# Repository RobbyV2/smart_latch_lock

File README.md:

# Folding-Arc Bike Lock

A self-closing bike lock built as a clamshell ring. A fixed arc bolts to the housing, a hinged arc swings 180 degrees to meet it, and a worm gearmotor closes the loop around the frame and rim on a button press or a BLE command. A spring latch pin seats with power off, a keyed cam lock covers a dead battery, and an ESP32-C3 on a 4-layer PCB runs the state machine.

<table>
<tr>
<td></td>
<td></td>
</tr>
</table>

The animation shows one closing cycle: the swing arc starts folded open and sweeps around until it seats in the receiver at the fixed arc tip.

<table>
<tr>
<td></td>
<td></td>
<td></td>
</tr>
</table>

Read `docs/design.md` for the mechanism, the torque analysis, and the electronics.

## Repository layout

- `hw/` holds the KiCad schematic, the board, the design rules, and the stack manifest.
- `lib/` holds the symbols, the footprints, and the 3D models.
- `firmware/` holds the PlatformIO project for the ESP32-C3.
- `3d/` holds the OpenSCAD housing, the board render script, and the renders.
- `scripts/` holds the release script and the validation scripts.
- `fab/` holds the fabrication data, written by `scripts/release.sh`.

## Build

```
pio run -d firmware
openscad -o temp/arc_swing.stl -D 'part="arc_swing"' 3d/housing.scad
python3 3d/build.py
scripts/release.sh hw/triangle_flywheel_balancer.kicad_pcb
```

The first command builds the firmware, the second renders one housing part (`housing_inner`, `housing_lid`, `arc_fixed`, `arc_swing`, `latch_pin`, `assembly`), the third writes the board renders and the viewer page, and the fourth writes the fabrication tree.

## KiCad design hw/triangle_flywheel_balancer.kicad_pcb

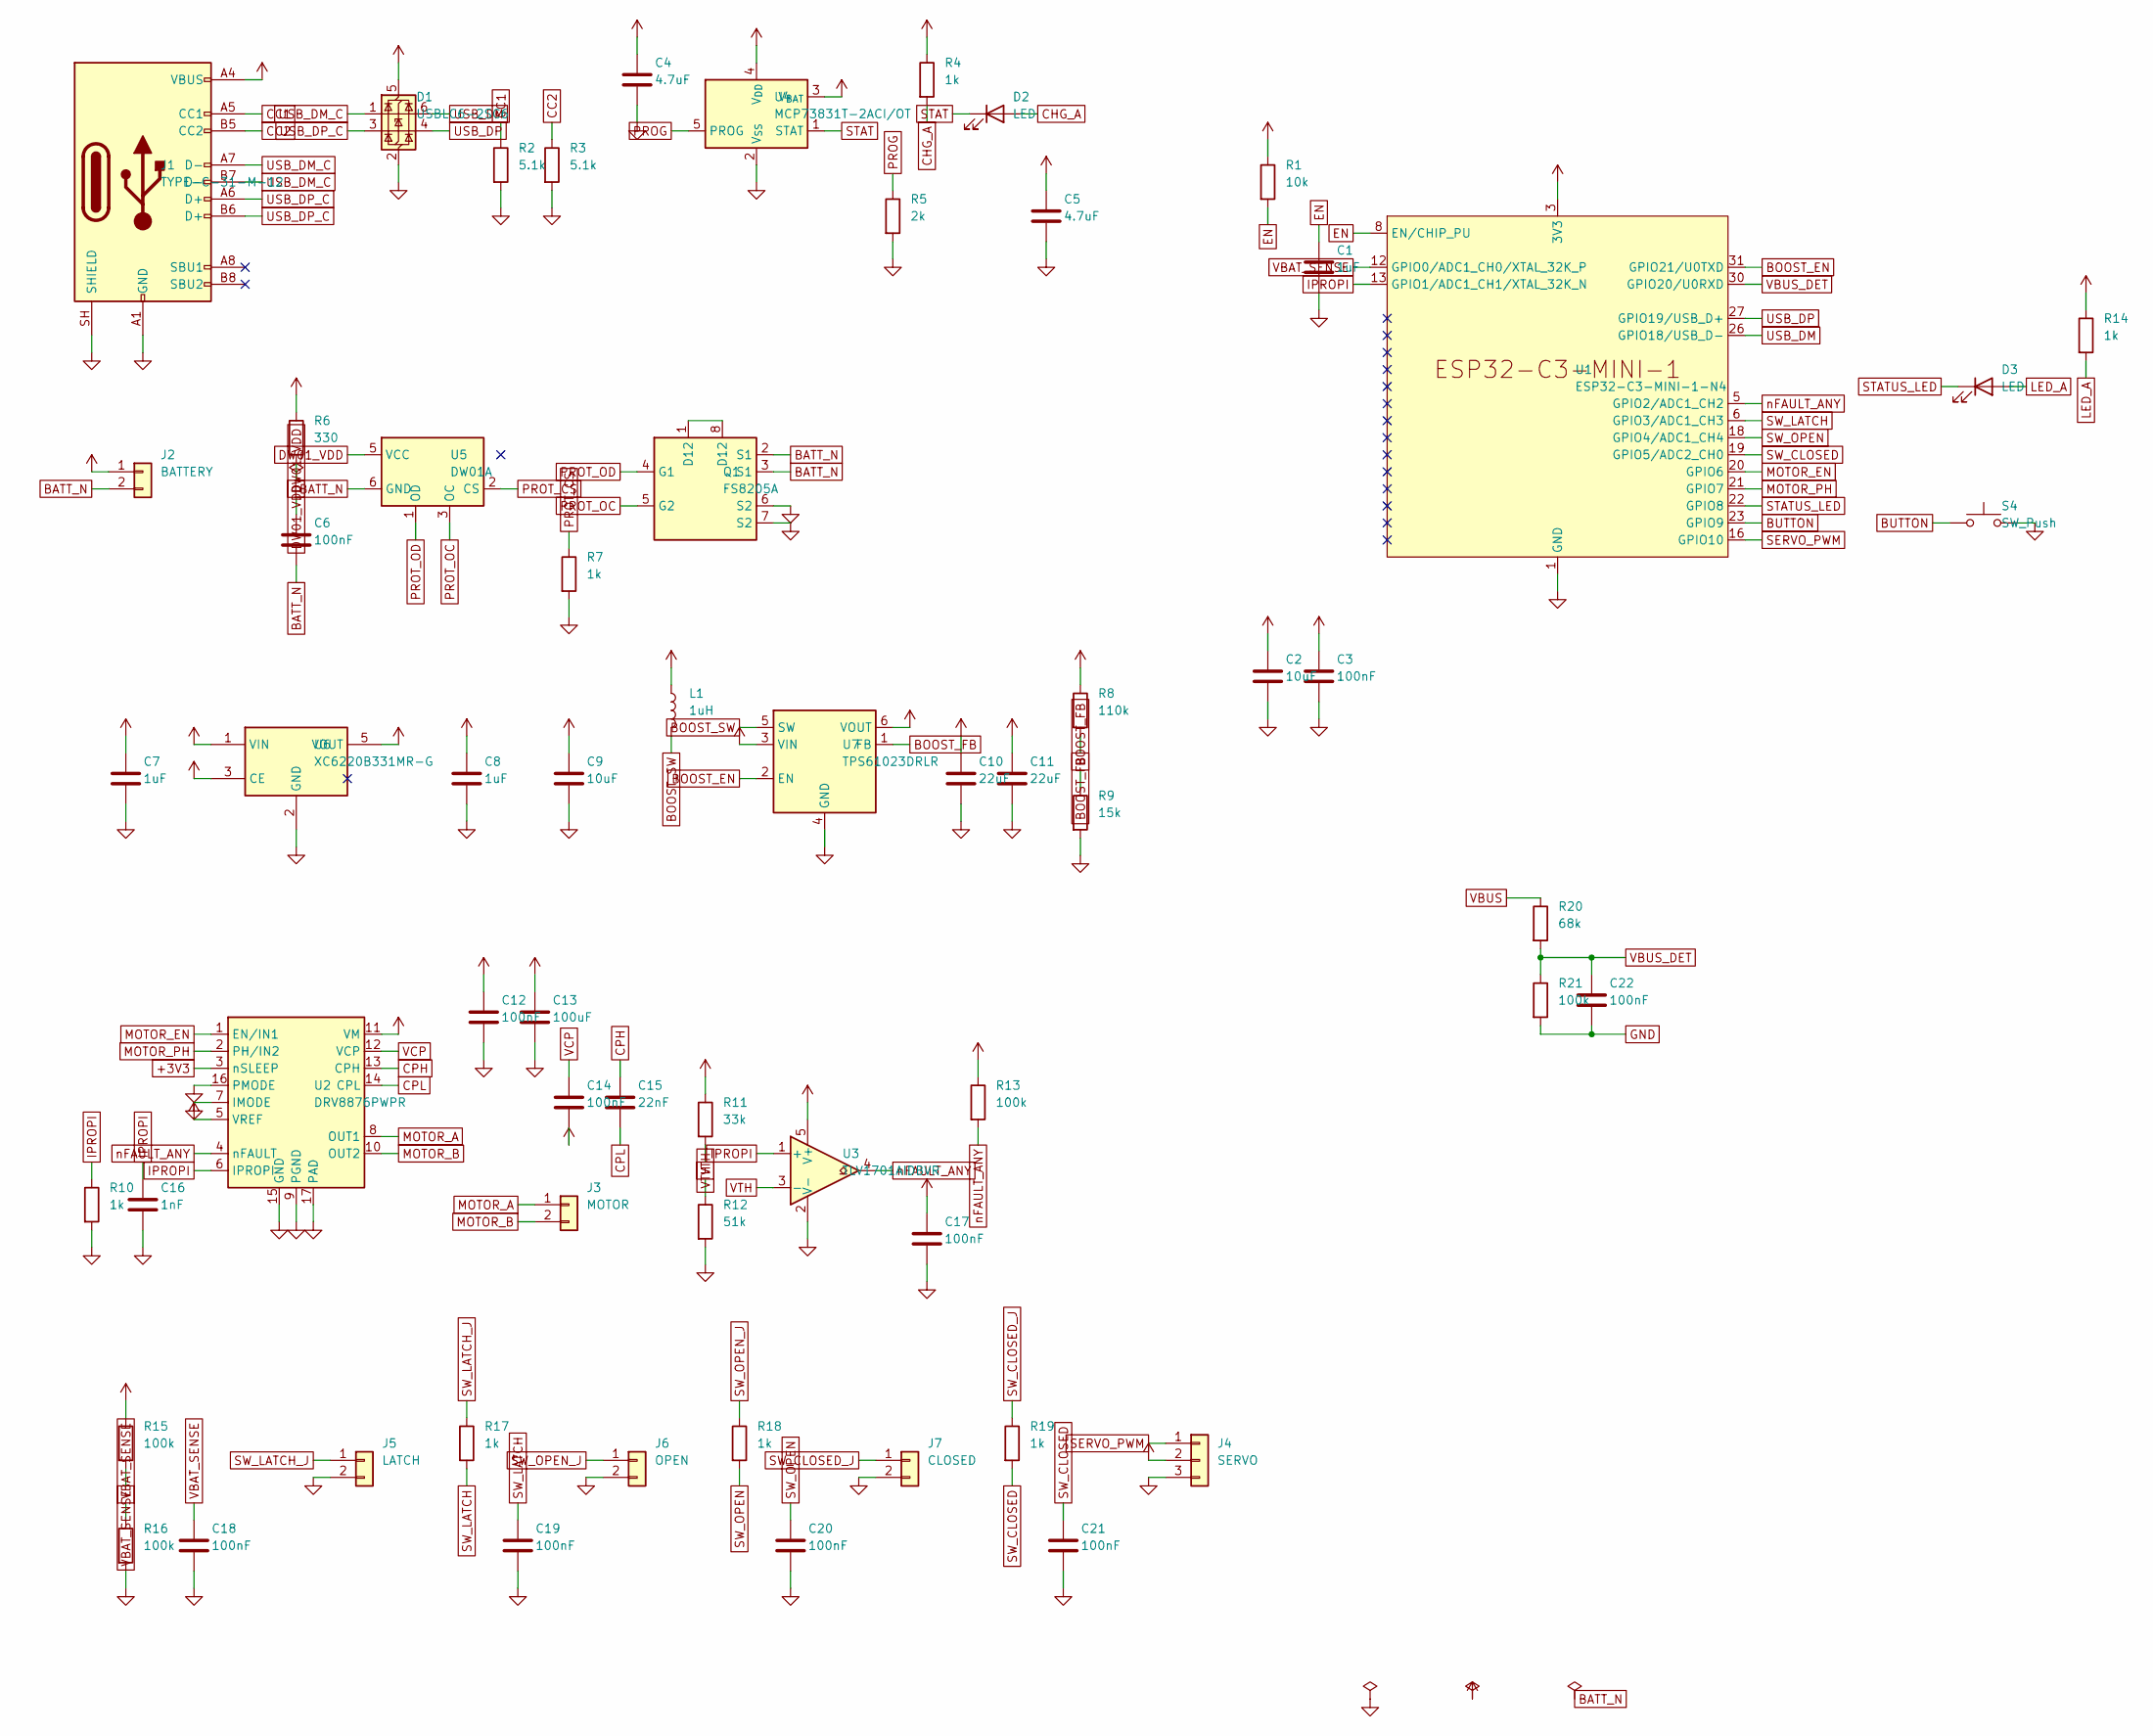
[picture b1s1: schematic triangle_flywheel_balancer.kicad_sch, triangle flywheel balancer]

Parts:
C1, C7, C8: 1uF; C_0603_1608Metric; MPN CL10A105KB8NNNC; LCSC Part C15849
C2, C9: 10uF; C_0805_2012Metric; MPN CL21A106KAYNNNE; LCSC Part C15850
C3, C6, C12, C14, C17, C18, C19, C20, C21, C22: 100nF; C_0402_1005Metric; MPN CL05B104KO5NNNC; LCSC Part C1525
C4, C5: 4.7uF; C_0603_1608Metric; MPN CL10A475KO8NNNC; LCSC Part C19666
C10, C11: 22uF; C_0805_2012Metric; MPN CL21A226MAQNNNE; LCSC Part C45783
C13: 100uF; C_1210_3225Metric; MPN CL32A107MPVNNNE; LCSC Part C23742
C15: 22nF; C_0402_1005Metric; MPN CL05B223KB5NNNC; LCSC Part C337699
C16: 1nF; C_0402_1005Metric; MPN 0402B102K500NT; LCSC Part C1523
D1: USBLC6-2SC6; SOT-23-6; MPN USBLC6-2SC6; LCSC Part C7519
D2, D3: LED; LED_0603_1608Metric; MPN KT-0603R; LCSC Part C2286
J1: TYPE-C-31-M-12; USB_C_Receptacle_HRO_TYPE-C-31-M-12; MPN TYPE-C-31-M-12; LCSC Part C165948
J2: BATTERY; JST_PH_B2B-PH-K_1x02_P2.00mm_Vertical; MPN B2B-PH-K-S(LF)(SN); LCSC Part C131337
J3: MOTOR; JST_PH_B2B-PH-K_1x02_P2.00mm_Vertical; MPN B2B-PH-K-S(LF)(SN); LCSC Part C131337
J4: SERVO; PinHeader_1x03_P2.54mm_Vertical; MPN 2.54-1*3P; LCSC Part C49257
J5: LATCH; PinHeader_1x02_P2.54mm_Vertical; MPN B-2100S02P-A110; LCSC Part C124375
J6: OPEN; PinHeader_1x02_P2.54mm_Vertical; MPN B-2100S02P-A110; LCSC Part C124375
J7: CLOSED; PinHeader_1x02_P2.54mm_Vertical; MPN B-2100S02P-A110; LCSC Part C124375
L1: 1uH; L_Murata_DFE201610P; MPN DFE201610E-1R0M=P2; LCSC Part C161082
Q1: FS8205A; TSSOP-8_4.4x3mm_P0.65mm; MPN 8205A; LCSC Part C5148694
R1: 10k; R_0402_1005Metric; MPN RC0402FR-0710KL; LCSC Part C60490
R2, R3: 5.1k; R_0402_1005Metric; MPN 0402WGF5101TCE; LCSC Part C25905
R4, R7, R10, R14, R17, R18, R19: 1k; R_0402_1005Metric; MPN 0402WGF1001TCE; LCSC Part C11702
R5: 2k; R_0402_1005Metric; MPN RC0402FR-072KL; LCSC Part C60488
R6: 330; R_0402_1005Metric; MPN 0402WGF3300TCE; LCSC Part C25104
R8: 110k; R_0402_1005Metric; MPN 0402WGF1103TCE; LCSC Part C25745
R9: 15k; R_0402_1005Metric; MPN 0402WGF1502TCE; LCSC Part C25756
R11: 33k; R_0402_1005Metric; MPN 0402WGF3302TCE; LCSC Part C25779
R12: 51k; R_0402_1005Metric; MPN 0402WGF5102TCE; LCSC Part C25794
R13, R15, R16, R21: 100k; R_0402_1005Metric; MPN 0402WGF1003TCE; LCSC Part C25741
R20: 68k; R_0402_1005Metric; MPN ERJ2RKF6802X; LCSC Part C77607
S4: SW_Push; SW_Push_1TS009xxxx-xxxx-xxxx_6x6x5mm; MPN TS-1187A-B-A-B; LCSC Part C318884
U1: ESP32-C3-MINI-1-N4; ESP32-C3-MINI-1; MPN ESP32-C3-MINI-1-N4; LCSC Part C2838502
U2: DRV8876PWPR; HTSSOP-16-1EP_4.4x5mm_P0.65mm_EP3.4x5mm_Mask3x3mm_ThermalVi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; MPN DRV8876PWPR; LCSC Part C575551
U3: TLV1701AIDBVR; SOT-23-5; MPN TLV1701AIDBVR; LCSC Part C130035
U4: MCP73831T-2ACI/OT; SOT-23-5; MPN MCP73831T-2ACI/OT; LCSC Part C424093
U5: DW01A; SOT-23-6; MPN DW01A; LCSC Part C351410
U6: XC6220B331MR-G; SOT-23-5; MPN XC6220B331MR-G; LCSC Part C86534
U7: TPS61023DRLR; SOT-563; MPN TPS61023DRLR; LCSC Part C919459

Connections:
+3V3: C2.1, C3.1, C8.1, C17.1, R1.1, R11.1, R13.1, R14.1, U1.3 (3V3), U2.3 (nSLEEP), U2.5 (VREF), U3.5 (V+), U6.5 (VOUT)
+5V: C10.1, C11.1, C12.1, C13.1, C14.2, J4.2, R8.1, U2.11 (VM), U7.6 (VOUT)
BATT_N: C6.2, J2.2, Q1.2 (S1), Q1.3 (S1), U5.6 (GND)
BOOST_EN: U1.31 (GPIO21/U0TXD), U7.2 (EN)
BOOST_FB: R8.2, R9.1, U7.1 (FB)
BOOST_SW: L1.2, U7.5 (SW)
BUTTON: S4.1, U1.23 (GPIO9)
CC1: J1.A5 (CC1), R2.1
CC2: J1.B5 (CC2), R3.1
CHG_A: D2.2 (A), R4.2
CPH: C15.1, U2.13 (CPH)
CPL: C15.2, U2.14 (CPL)
DW01_VDD: C6.1, R6.2, U5.5 (VCC)
EN: C1.1, R1.2, U1.8 (EN/CHIP_PU)
GND: C1.2, C2.2, C3.2, C4.2, C5.2, C7.2, C8.2, C9.2, C10.2, C11.2, C12.2, C13.2, C16.2, C17.2, C18.2, C19.2, C20.2, C21.2, C22.2, D1.2 (GND), J1.A1 (GND), J1.A12 (GND), J1.B1 (GND), J1.B12 (GND), J1.SH (SHIELD), J4.3, J5.2, J6.2, J7.2, Q1.6 (S2), Q1.7 (S2), R2.2, R3.2, R5.2, R7.2, R9.2, R10.2, R12.2, R16.2, R21.2, S4.2, U1.1 (GND), U1.2 (GND), U1.11 (GND), U1.14 (GND), U1.36 (GND), U1.37 (GND), U1.38 (GND), U1.39 (GND), U1.40 (GND), U1.41 (GND), U1.42 (GND), U1.43 (GND), U1.44 (GND), U1.45 (GND), U1.46 (GND), U1.47 (GND), U1.48 (GND), U1.49 (GND), U1.50 (GND), U1.51 (GND), U1.52 (GND), U1.53 (GND), U2.7 (IMODE), U2.9 (PGND), U2.15 (GND), U2.16 (PMODE), U2.17 (PAD), U3.2 (V-), U4.2 (V_{SS}), U6.2 (GND), U7.4 (GND)
IPROPI: C16.1, R10.1, U1.13 (GPIO1/ADC1_CH1/XTAL_32K_N), U2.6 (IPROPI), U3.1 (+)
LED_A: D3.2 (A), R14.2
MOTOR_A: J3.1, U2.8 (OUT1)
MOTOR_B: J3.2, U2.10 (OUT2)
MOTOR_EN: U1.20 (GPIO6), U2.1 (EN/IN1)
MOTOR_PH: U1.21 (GPIO7), U2.2 (PH/IN2)
unnamed: Q1.1 (D12), Q1.8 (D12)
PROG: R5.1, U4.5 (PROG)
PROT_CS: R7.1, U5.2 (CS)
PROT_OC: Q1.5 (G2), U5.3 (OC)
PROT_OD: Q1.4 (G1), U5.1 (OD)
SERVO_PWM: J4.1, U1.16 (GPIO10)
STAT: D2.1 (K), U4.1 (STAT)
STATUS_LED: D3.1 (K), U1.22 (GPIO8)
SW_CLOSED: C21.1, R19.2, U1.19 (GPIO5/ADC2_CH0)
SW_CLOSED_J: J7.1, R19.1
SW_LATCH: C19.1, R17.2, U1.6 (GPIO3/ADC1_CH3)
SW_LATCH_J: J5.1, R17.1
SW_OPEN: C20.1, R18.2, U1.18 (GPIO4/ADC1_CH4)
SW_OPEN_J: J6.1, R18.1
USB_DM: D1.6 (I/O1), U1.26 (GPIO18/USB_D-)
USB_DM_C: D1.1 (I/O1), J1.A7 (D-), J1.B7 (D-)
USB_DP: D1.4 (I/O2), U1.27 (GPIO19/USB_D+)
USB_DP_C: D1.3 (I/O2), J1.A6 (D+), J1.B6 (D+)
VBAT: C5.1, C7.1, C9.1, J2.1, L1.1, R6.1, R15.1, U4.3 (V_{BAT}), U6.1 (VIN), U6.3 (CE), U7.3 (VIN)
VBAT_SENSE: C18.1, R15.2, R16.1, U1.12 (GPIO0/ADC1_CH0/XTAL_32K_P)
VBUS: C4.1, D1.5 (VBUS), J1.A4 (VBUS), J1.A9 (VBUS), J1.B4 (VBUS), J1.B9 (VBUS), R4.1, R20.1, U4.4 (V_{DD})
VBUS_DET: C22.1, R20.2, R21.1, U1.30 (GPIO20/U0RXD)
VCP: C14.1, U2.12 (VCP)
VTH: R11.2, R12.1, U3.3 (-)
nFAULT_ANY: R13.2, U1.5 (GPIO2/ADC1_CH2), U2.4 (nFAULT), U3.4

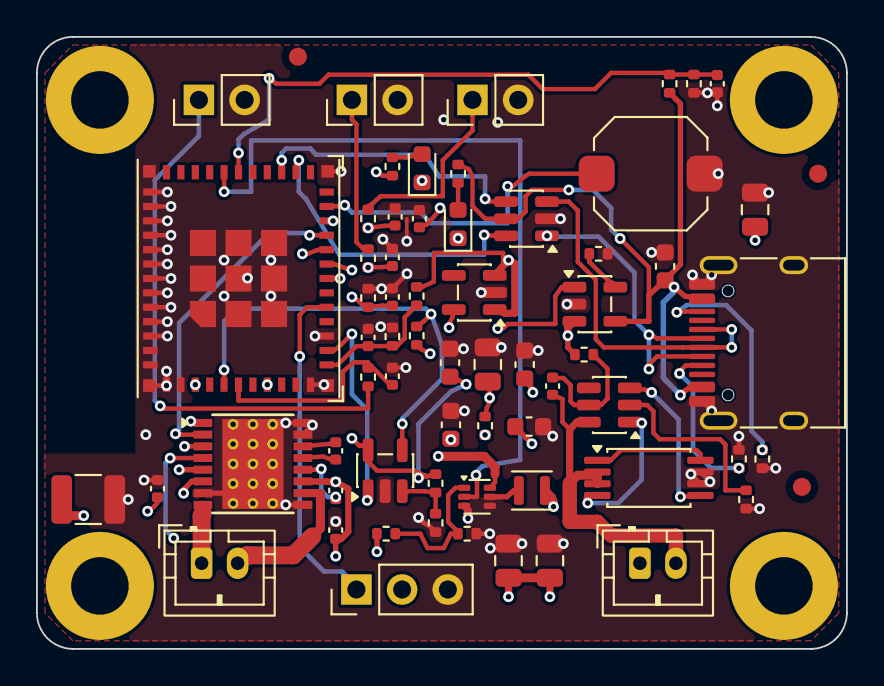
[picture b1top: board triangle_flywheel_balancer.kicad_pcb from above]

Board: 4 copper layers, 45.0 x 34.0 mm, 70 parts (0 on the bottom side), 46 nets.

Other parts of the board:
FID1, FID2, FID3: Fiducial; Fiducial_1mm_Mask2mm
H1, H2, H3, H4: MountingHole; MountingHole_3.2mm_M2.5

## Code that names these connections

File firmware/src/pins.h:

#pragma once
#include <stdint.h>

constexpr int PIN_VBAT_SENSE = 0;
constexpr int PIN_IPROPI = 1;
constexpr int PIN_NFAULT = 2;
constexpr int PIN_SW_LATCH = 3;
constexpr int PIN_SW_OPEN = 4;
constexpr int PIN_SW_CLOSED = 5;
constexpr int PIN_MOTOR_EN = 6;
constexpr int PIN_MOTOR_PH = 7;
constexpr int PIN_LED = 8;
constexpr int PIN_BUTTON = 9;
constexpr int PIN_SERVO = 10;
constexpr int PIN_VBUS_DET = 20;
constexpr int PIN_BOOST_EN = 21;

constexpr uint32_t INRUSH_MASK_US = 120000;
constexpr uint32_t MOTOR_TIMEOUT_MS = 3000;
constexpr uint32_t LATCH_TIMEOUT_MS = 500;
constexpr uint32_t UNLATCH_TIMEOUT_MS = 300;
constexpr uint32_t BTN_HOLD_MS = 3000;
constexpr uint32_t BLE_GRACE_MS = 5000;
constexpr int SOFT_STALL_MV = 1200;
constexpr int SOFT_STALL_SAMPLES = 20;
constexpr int VBAT_MIN_LOCK_MV = 3300;
constexpr uint32_t SERVO_RETRACT_US = 1000;
constexpr uint32_t SERVO_RELEASE_US = 2000;
constexpr uint32_t BOOST_OFF_MS = 50;

constexpr char UUID_SVC[] = "8f1d0001-2f3a-4c6e-9b1d-6a0f5e3c7a42";
constexpr char UUID_CMD[] = "8f1d0002-2f3a-4c6e-9b1d-6a0f5e3c7a42";
constexpr char UUID_STATE[] = "8f1d0003-2f3a-4c6e-9b1d-6a0f5e3c7a42";

enum class State : uint8_t {
  UnlockedOpen, Closing, Seating, Locked, Unlatching, Opening, FaultObstructed, FaultTimeout
};
enum class Event : uint8_t {
  CmdLock, CmdUnlock, CmdClear, BtnShort, BtnHold3, EsClosed, EsOpen,
  LatchSeated, LatchClear, Stall, Timeout, Raw
};

constexpr uint8_t F_STALL_HW = 0x01, F_STALL_SOFT = 0x02, F_TIMEOUT = 0x04, F_LATCH = 0x08, F_LOWBAT = 0x10, F_CHARGING = 0x20;
